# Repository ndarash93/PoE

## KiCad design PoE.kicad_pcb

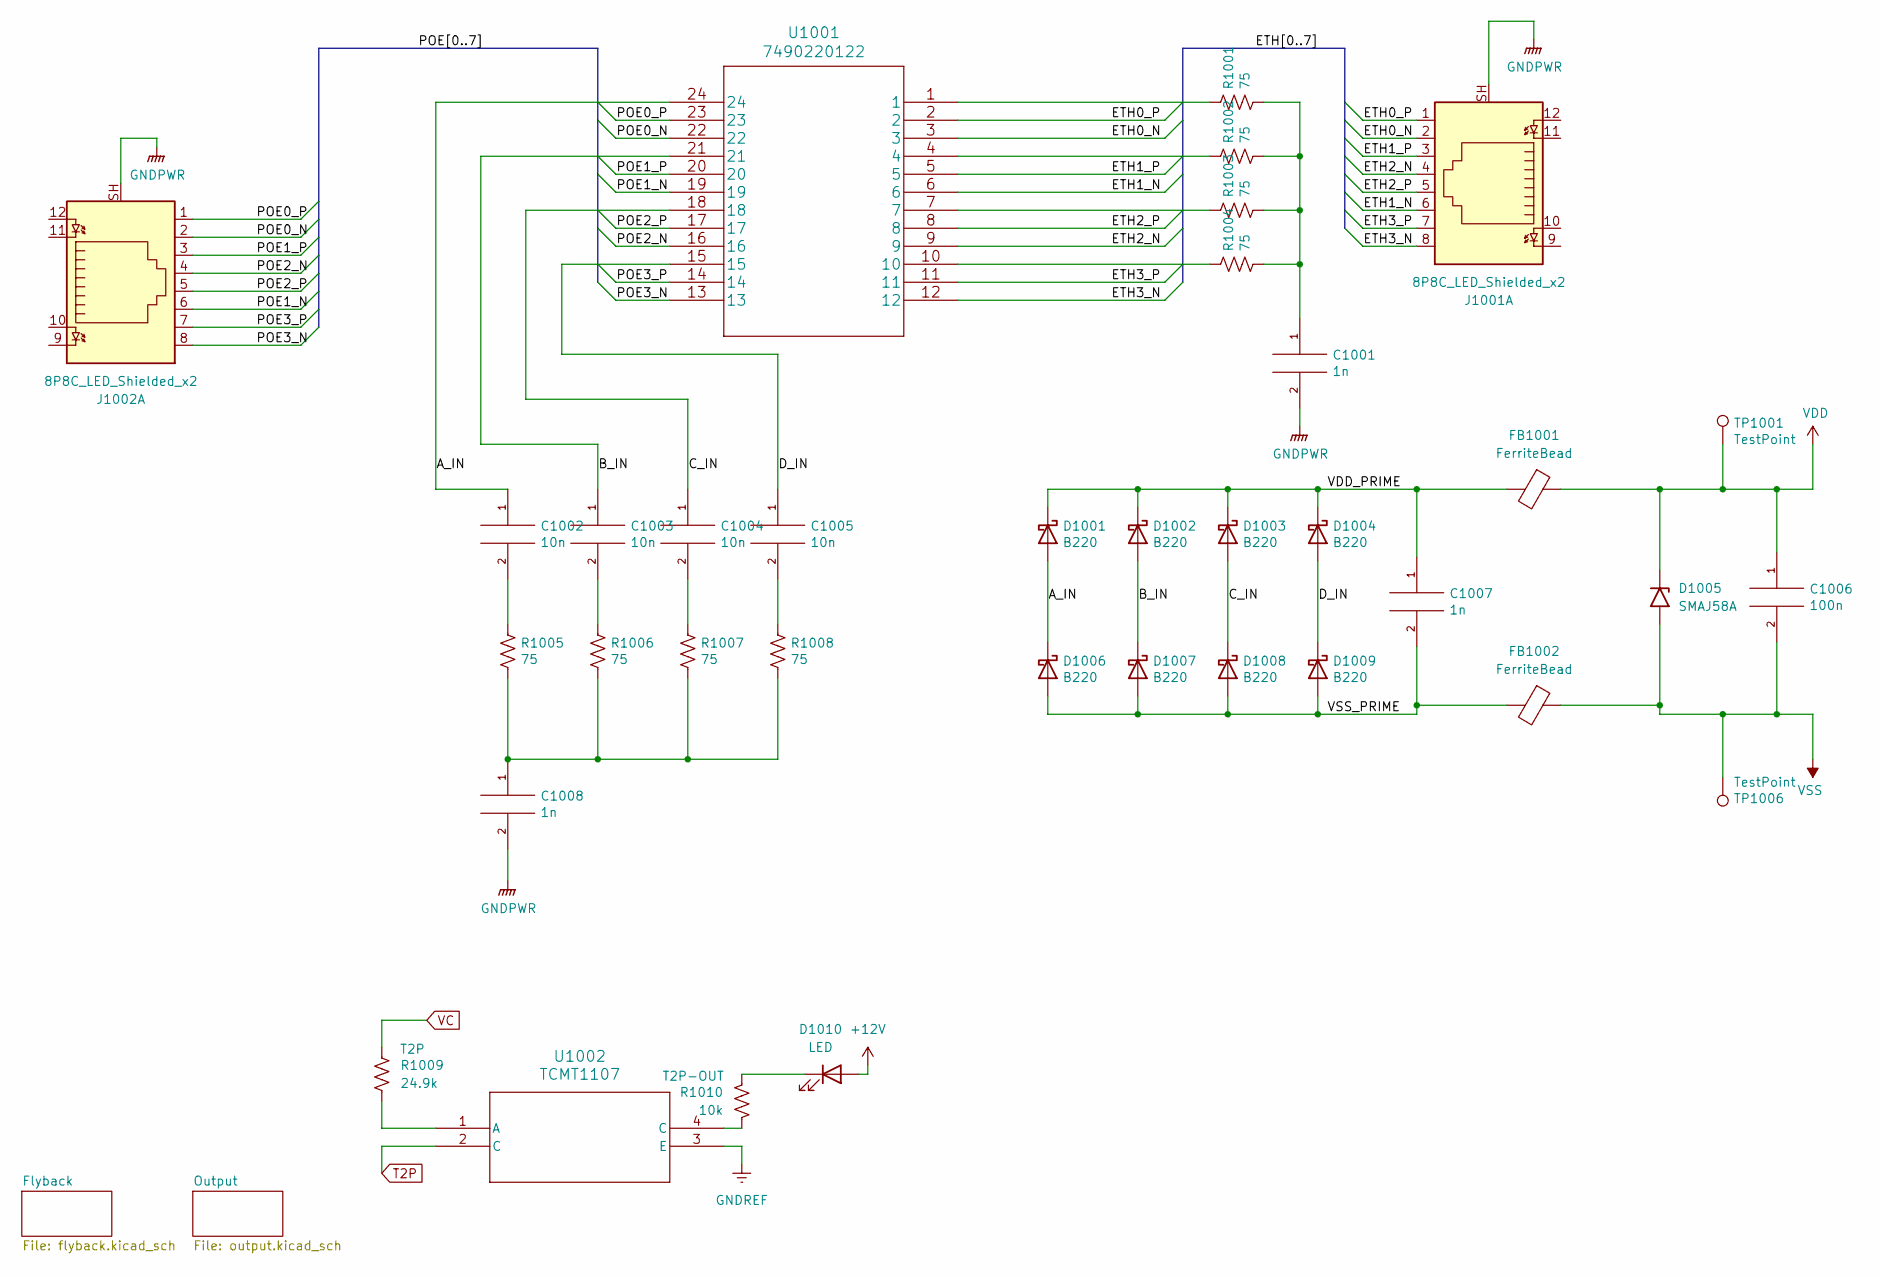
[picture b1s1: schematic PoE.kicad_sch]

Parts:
C1001, C1007, C1008: 1n; C_0805_2012Metric
C1002, C1003, C1004, C1005: 10n; C_0805_2012Metric
C1006: 100n; C_0805_2012Metric
D1001, D1002, D1003, D1004, D1006, D1007, D1008, D1009: B220; D_SMB
D1005: SMAJ58A; D_SMA
D1010: LED; LED_0805_2012Metric
FB1001, FB1002: FerriteBead; R_0805_2012Metric
J1001, J1002: 8P8C_LED_Shielded_x2; CONN12_ARJM11B1-009-AB-EW2_ABR
R1001, R1002, R1003, R1004, R1005, R1006, R1007, R1008: 75; R_0805_2012Metric
R1009: 24.9k; R_0805_2012Metric
R1010: 10k; R_0805_2012Metric
TP1001, TP1006: TestPoint; TestPoint_Pad_1.0x1.0mm
U1001: 7490220122
U1002: TCMT1107; SSOP4_4P40X2P85_VIS

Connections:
+12V: D1010.2 (A); also elsewhere on the board
/A_IN: C1002.1, D1001.2 (A), D1006.1 (K), U1001.24
/B_IN: C1003.1, D1002.2 (A), D1007.1 (K), U1001.21
/C_IN: C1004.1, D1003.2 (A), D1008.1 (K), U1001.18
/D_IN: C1005.1, D1004.2 (A), D1009.1 (K), U1001.15
/ETH0_N: J1001.2, U1001.3
/ETH0_P: J1001.1, U1001.2
/ETH1_N: J1001.6, U1001.6
/ETH1_P: J1001.3, U1001.5
/ETH2_N: J1001.4, U1001.9
/ETH2_P: J1001.5, U1001.8
/ETH3_N: J1001.8, U1001.12
/ETH3_P: J1001.7, U1001.11
/POE0_N: J1002.2, U1001.22
/POE0_P: J1002.1, U1001.23
/POE1_N: J1002.6, U1001.19
/POE1_P: J1002.3, U1001.20
/POE2_N: J1002.4, U1001.16
/POE2_P: J1002.5, U1001.17
/POE3_N: J1002.8, U1001.13
/POE3_P: J1002.7, U1001.14
/VDD_PRIME: C1007.1, D1001.1 (K), D1002.1 (K), D1003.1 (K), D1004.1 (K), FB1001.2
/VSS_PRIME: C1007.2, D1006.2 (A), D1007.2 (A), D1008.2 (A), D1009.2 (A), FB1002.2
GNDPWR: C1001.2, C1008.2, J1001.SH, J1002.SH
GNDREF: U1002.3 (E); also elsewhere on the board
unnamed: C1001.1, R1001.2, R1002.2, R1003.2, R1004.2
unnamed: C1002.2, R1005.1
unnamed: C1003.2, R1006.1
unnamed: C1004.2, R1007.1
unnamed: C1005.2, R1008.1
unnamed: C1008.1, R1005.2, R1006.2, R1007.2, R1008.2
unnamed: D1010.1 (K), R1010.1
unnamed: R1001.1, U1001.1
unnamed: R1002.1, U1001.4
unnamed: R1003.1, U1001.7
unnamed: R1004.1, U1001.10
unnamed: R1010.2, U1002.4 (C)
unnamed: R1009.2, U1002.1 (A)
T2P: U1002.2 (C); also elsewhere on the board
VC: R1009.1; also elsewhere on the board
VDD: C1006.1, D1005.1 (A1), FB1001.1, TP1001.1; also elsewhere on the board
VSS: C1006.2, D1005.2 (A2), FB1002.1, TP1006.1; also elsewhere on the board

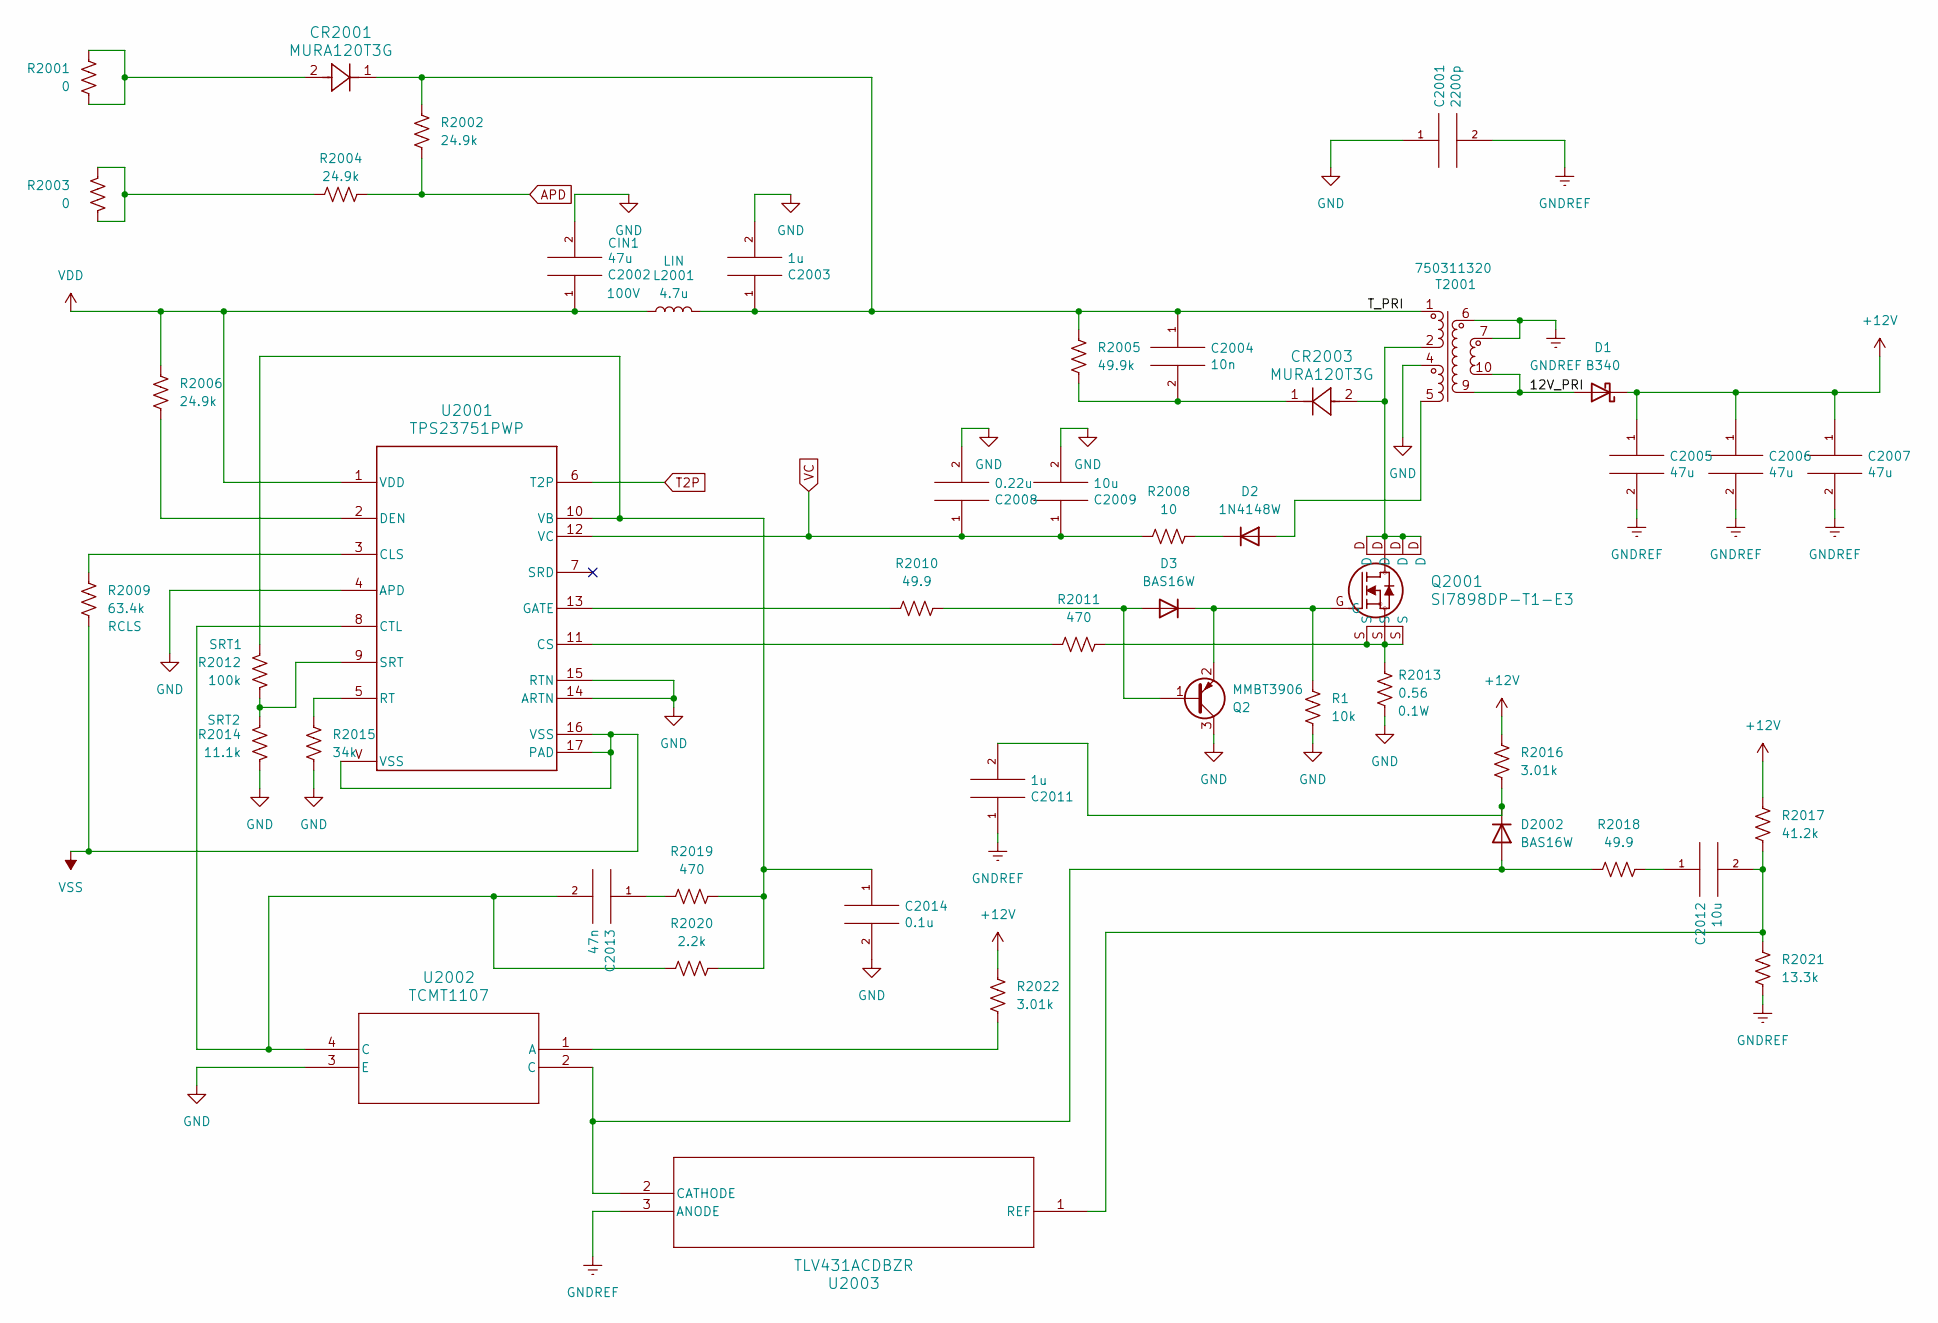
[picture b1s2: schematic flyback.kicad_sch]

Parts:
C2001: 2200p; C_0805_2012Metric
C2002: 47u; CAP_WCAP-ASLI_06p3X05p5_WRE; Voltage 100V
C2003: 1u; CAP_WCAP-ASLI_06p3X05p5_WRE
C2004: 10n; C_0805_2012Metric
C2005, C2006, C2007: 47u; CAP_WCAP-ASLI_06p3X05p5_WRE
C2008: 0.22u; C_0805_2012Metric
C2009, C2012: 10u; C_0805_2012Metric
C2011: 1u; C_0805_2012Metric
C2013: 47n; C_0805_2012Metric
C2014: 0.1u; C_0805_2012Metric
CR2001, CR2003: MURA120T3G; DIODE_TVS1SMAS5_4P57X2P92_ONS
D1: B340; D_SMC
D2: 1N4148W; D_SOD-123
D3, D2002: BAS16W; SOT-323_SC-70
L2001: 4.7u; L_Abracon_ASPI-4030S
Q2: MMBT3906; SOT-23
Q2001: SI7898DP-T1-E3; MOSFET_50DP-T1-E3_VIS
R1: 10k; R_0805_2012Metric
R2001, R2003: 0; R_0805_2012Metric
R2002, R2004, R2006: 24.9k; R_0805_2012Metric
R2005: 49.9k; R_0805_2012Metric
R2008: 10; R_0805_2012Metric
R2009: 63.4k; R_0805_2012Metric
R2010, R2018: 49.9; R_0805_2012Metric
R2011, R2019: 470; R_0805_2012Metric
R2012: 100k; R_0805_2012Metric
R2013: 0.56; R_0805_2012Metric
R2014: 11.1k; R_0805_2012Metric
R2015: 34k; R_0805_2012Metric
R2016, R2022: 3.01k; R_0805_2012Metric
R2017: 41.2k; R_0805_2012Metric
R2020: 2.2k; R_0805_2012Metric
R2021: 13.3k; R_0805_2012Metric
T2001: 750311320
U2001: TPS23751PWP; PWP0016J_N
U2002: TCMT1107; SSOP4_4P40X2P85_VIS
U2003: TLV431ACDBZR; DBZ3

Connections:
+12V: C2005.1, C2006.1, C2007.1, D1.1 (K), R2016.2, R2017.1, R2022.2; also elsewhere on the board
/Flyback/12V_PRI: D1.2 (A), T2001.9, T2001.10
/Flyback/T_PRI: C2003.1, C2004.1, CR2001.1, L2001.2, R2002.1, R2005.1, T2001.1
APD: R2002.2, R2004.1
GND: C2001.1, C2002.2, C2003.2, C2008.2, C2009.2, C2014.2, Q2.3 (C), R1.2, R2013.2, R2014.2, R2015.2, T2001.4, U2001.4 (APD), U2001.14 (ARTN), U2001.15 (RTN), U2002.3 (E)
GNDREF: C2001.2, C2005.2, C2006.2, C2007.2, C2011.1, R2021.2, T2001.6, T2001.7, U2003.3 (ANODE); also elsewhere on the board
unnamed: C2004.2, CR2003.1, R2005.2
unnamed: C2012.1, R2018.1
unnamed: C2013.1, R2019.2
unnamed: CR2001.2, R2001.1, R2001.2
unnamed: CR2003.2, Q2001.D, T2001.2
unnamed: D2.2 (A), T2001.5
unnamed: D2.1 (K), R2008.1
unnamed: D3.1 (A), Q2.1 (B), R2010.1
unnamed: D3.3 (K), Q2.2 (E), Q2001.G, R1.1
unnamed: D2002.1 (A), R2018.2, U2002.2 (C), U2003.2 (CATHODE)
unnamed: C2011.2, D2002.3 (K), R2016.1
unnamed: Q2001.S, R2011.1, R2013.1
unnamed: R2003.1, R2003.2, R2004.2
unnamed: R2009.1, U2001.3 (CLS)
unnamed: R2011.2, U2001.11 (CS)
unnamed: C2013.2, R2020.2, U2001.8 (CTL), U2002.4 (C)
unnamed: R2006.2, U2001.2 (DEN)
unnamed: R2010.2, U2001.13 (GATE)
unnamed: R2015.1, U2001.5 (RT)
unnamed: R2012.2, R2014.1, U2001.9 (SRT)
unnamed: C2014.1, R2012.1, R2019.1, R2020.1, U2001.10 (VB)
unnamed: R2022.1, U2002.1 (A)
unnamed: C2012.2, R2017.2, R2021.1, U2003.1 (REF)
T2P: U2001.6 (T2P); also elsewhere on the board
VC: C2008.1, C2009.1, R2008.2, U2001.12 (VC); also elsewhere on the board
VDD: C2002.1, L2001.1, R2006.1, U2001.1 (VDD); also elsewhere on the board
VSS: R2009.2, U2001.16 (VSS), U2001.17 (PAD), U2001.V (VSS); also elsewhere on the board

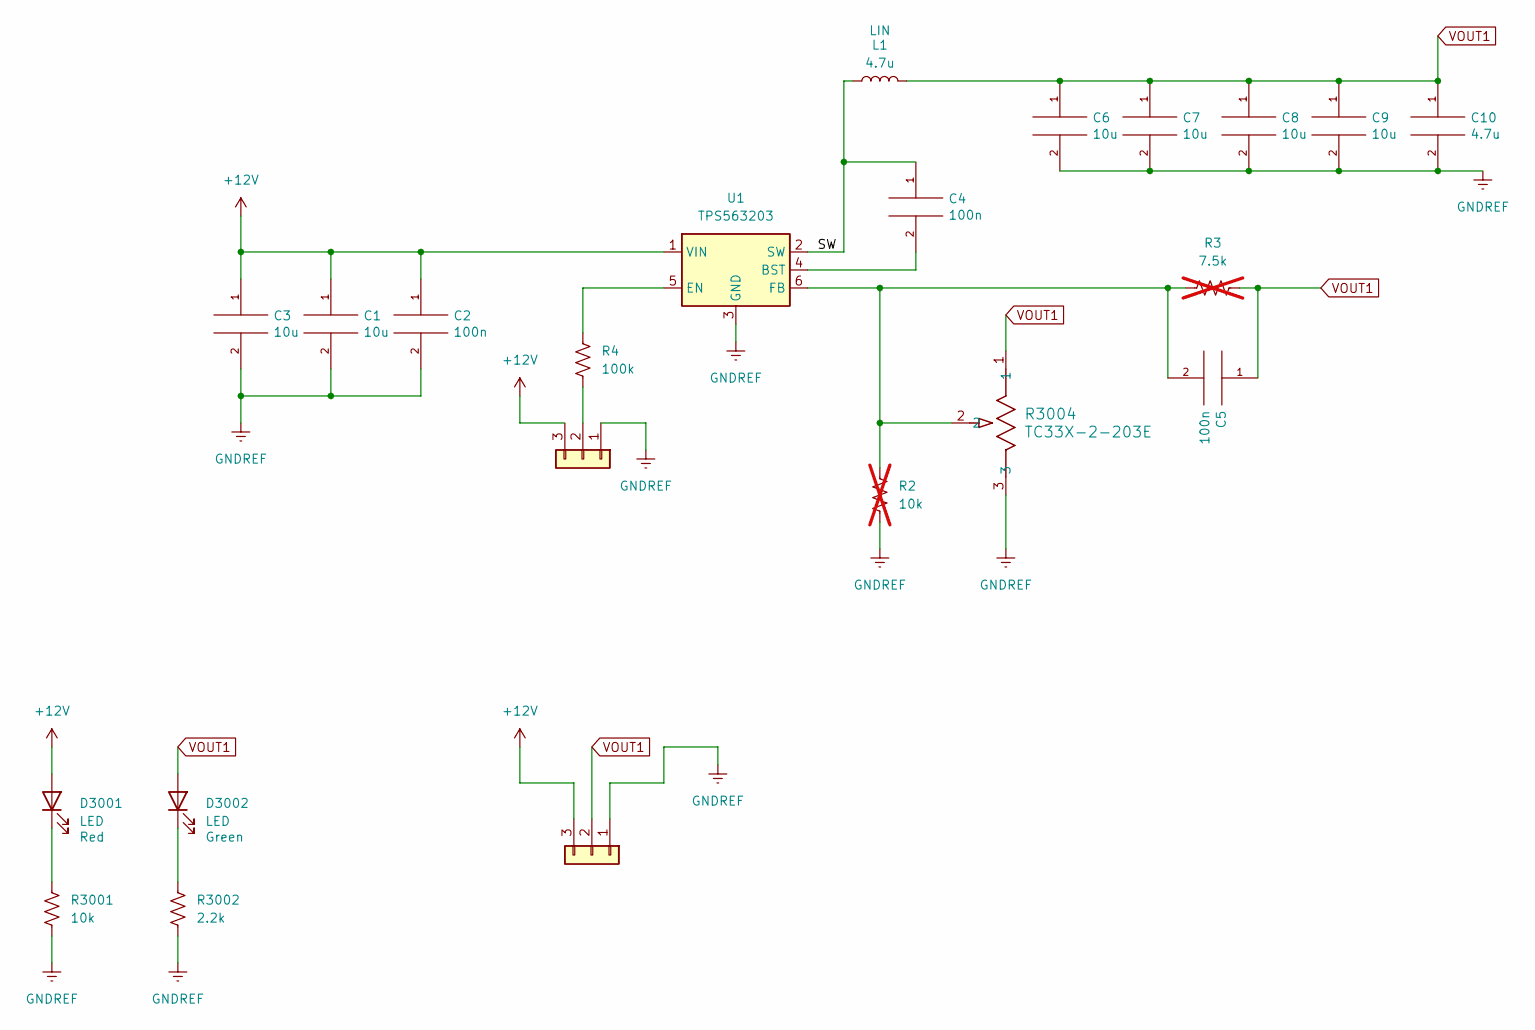
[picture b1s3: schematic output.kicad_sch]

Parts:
C1, C3, C6, C7, C8, C9: 10u; C_0805_2012Metric
C2, C4, C5: 100n; C_0805_2012Metric
C10: 4.7u; C_0805_2012Metric
D3001, D3002: LED; LED_0805_2012Metric
J1, J3001: Conn_01x03; 1x03
L1: 4.7u; L_Abracon_ASPI-4030S
R2: 10k; R_0805_2012Metric; not fitted
R3: 7.5k; R_0805_2012Metric; not fitted
R4: 100k; R_0805_2012Metric
R3001: 10k; R_0805_2012Metric
R3002: 2.2k; R_0805_2012Metric
R3004: TC33X-2-203E; Potentiometer_Bourns_TC33X_Vertical
U1: TPS563203; SOT-563

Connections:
+12V: C1.1, C2.1, C3.1, D3001.2 (A), J1.3, J3001.3, U1.1 (VIN); also elsewhere on the board
/Output/SW: C4.1, L1.1, U1.2 (SW)
GNDREF: C1.2, C2.2, C3.2, C6.2, C7.2, C8.2, C9.2, C10.2, J1.1, J3001.1, R2.1, R3001.1, R3002.1, R3004.3, U1.3 (GND); also elsewhere on the board
unnamed: D3001.1 (K), R3001.2
unnamed: D3002.1 (K), R3002.2
unnamed: J1.2, R4.1
unnamed: C4.2, U1.4 (BST)
unnamed: R4.2, U1.5 (EN)
unnamed: C5.2, R2.2, R3.1, R3004.2, U1.6 (FB)
VOUT1: C5.1, C6.1, C7.1, C8.1, C9.1, C10.1, D3002.2 (A), J3001.2, L1.2, R3.2, R3004.1

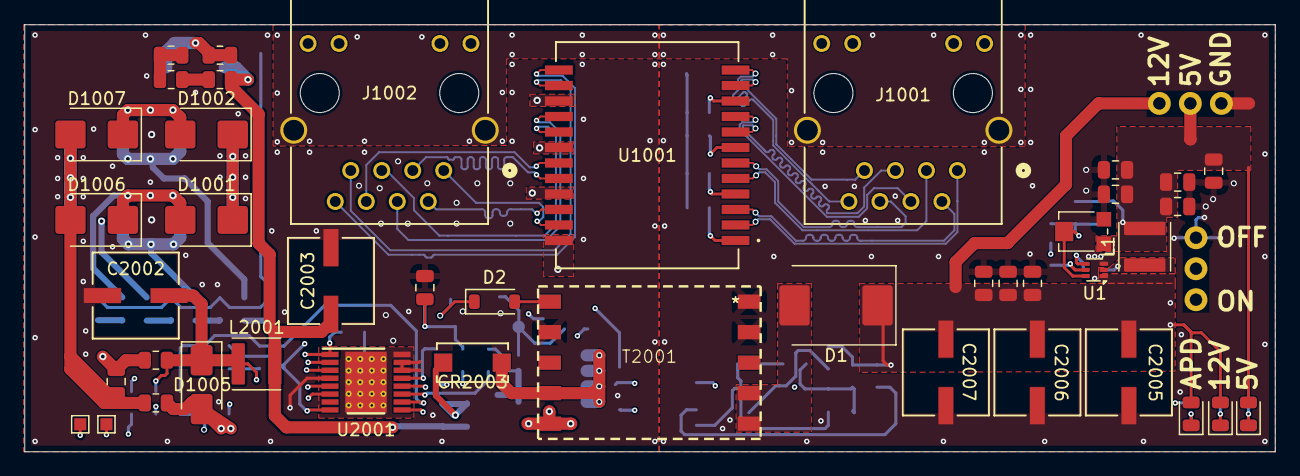
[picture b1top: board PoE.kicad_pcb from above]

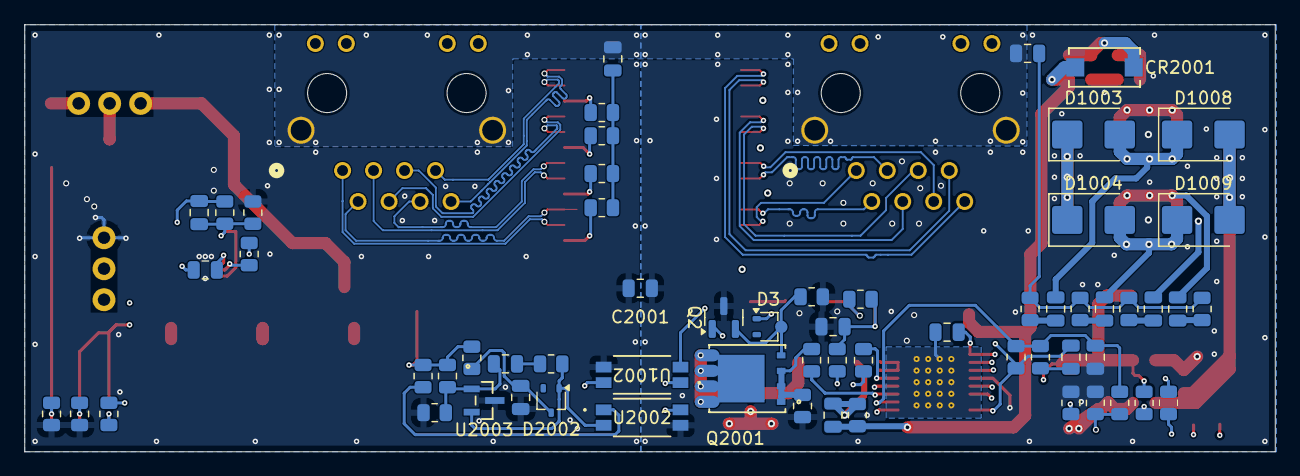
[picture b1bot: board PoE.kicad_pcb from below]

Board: 4 copper layers, 102.5 x 35.0 mm, 106 parts (61 on the bottom side), 77 nets.

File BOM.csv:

"Reference","Value","Datasheet","Footprint","Qty","DNP"
"C1,C3,C6,C7,C8,C9,C2009,C2012","10u","~","-- mixed values --","8",""
"C2,C4,C5,C1006","100n","~","Capacitor_SMD:C_0805_2012Metric","4",""
"C10,L1,L2001","4.7u","~","-- mixed values --","3",""
"C1001,C1007,C1008","1n","~","Capacitor_SMD:C_0805_2012Metric","3",""
"C1002,C1003,C1004,C1005,C2004","10n","~","Capacitor_SMD:C_0805_2012Metric","5",""
"C2001","2200p","~","Capacitor_SMD:C_0805_2012Metric","1",""
"C2002,C2005,C2006,C2007","47u","~","footprints:CAP_WCAP-ASLI_06p3X05p5_WRE","4",""
"C2003,C2011","1u","~","Capacitor_SMD:C_0805_2012Metric","2",""
"C2008","0.22u","~","Capacitor_SMD:C_0805_2012Metric","1",""
"C2013","47n","~","Capacitor_SMD:C_0805_2012Metric","1",""
"C2014","0.1u","~","Capacitor_SMD:C_0805_2012Metric","1",""
"CR2001,CR2003","MURA120T3G","MURA120T3G","footprints:DIODE_TVS1SMAS5_4P57X2P92_ONS","2",""
"D1","B340","http://www.jameco.com/Jameco/Products/ProdDS/1538777.pdf","Diode_SMD:D_SMC","1",""
"D2","1N4148W","https://www.vishay.com/docs/85748/1n4148w.pdf","Diode_SMD:D_SOD-123","1",""
"D3,D2002","BAS16W","https://assets.nexperia.com/documents/data-sheet/BAS16_SER.pdf","Package_TO_SOT_SMD:SOT-323_SC-70","2",""
"D1001,D1002,D1003,D1004,D1006,D1007,D1008,D1009","B220","http://www.jameco.com/Jameco/Products/ProdDS/1538777.pdf","Diode_SMD:D_SMB","8",""
"D1005","SMAJ58A","https://www.littelfuse.com/media?resourcetype=datasheets&ite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","Diode_SMD:D_SMA","1",""
"D1010,D3001,D3002","LED","~","LED_SMD:LED_0805_2012Metric","3",""
"FB1001,FB1002","FerriteBead","~","Resistor_SMD:R_0805_2012Metric","2",""
"J1,J3001","Conn_01x03","~","SparkFun-Connector:1x03","2",""
"J1001,J1002","8P8C_LED_Shielded_x2","~","footprints:CONN12_ARJM11B1-009-AB-EW2_ABR","2",""
"Q2","MMBT3906","https://www.onsemi.com/pdf/datasheet/pzt3906-d.pdf","Package_TO_SOT_SMD:SOT-23","1",""
"Q2001","SI7898DP-T1-E3","SI7898DP-T1-E3","footprints:MOSFET_50DP-T1-E3_VIS","1",""
"R1,R1010,R3001","10k","~","Resistor_SMD:R_0805_2012Metric","3",""
"R2","10k","~","Resistor_SMD:R_0805_2012Metric","1","DNP"
"R3","7.5k","~","Resistor_SMD:R_0805_2012Metric","1","DNP"
"R4,R2012","100k","~","Resistor_SMD:R_0805_2012Metric","2",""
"R1001,R1002,R1003,R1004,R1005,R1006,R1007,R1008","75","~","Resistor_SMD:R_0805_2012Metric","8",""
"R1009,R2002,R2004,R2006","24.9k","~","Resistor_SMD:R_0805_2012Metric","4",""
"R2001,R2003","0","-- mixed values --","Resistor_SMD:R_0805_2012Metric","2",""
"R2005","49.9k","~","Resistor_SMD:R_0805_2012Metric","1",""
"R2008","10","~","Resistor_SMD:R_0805_2012Metric","1",""
"R2009","63.4k","~","Resistor_SMD:R_0805_2012Metric","1",""
"R2010","43.2","~","Resistor_SMD:R_0805_2012Metric","1",""
"R2011","332","~","Resistor_SMD:R_0805_2012Metric","1",""
"R2013","0.56","~","Resistor_SMD:R_0805_2012Metric","1",""
"R2014","11.1k","~","Resistor_SMD:R_0805_2012Metric","1",""
"R2015","34k","~","Resistor_SMD:R_0805_2012Metric","1",""
"R2016,R2022","3.01k","~","Resistor_SMD:R_0805_2012Metric","2",""
"R2017","41.2k","~","Resistor_SMD:R_0805_2012Metric","1",""
"R2018","49.9","~","Resistor_SMD:R_0805_2012Metric","1",""
"R2019","402","~","Resistor_SMD:R_0805_2012Metric","1",""
"R2020","2k","~","Resistor_SMD:R_0805_2012Metric","1",""
"R2021","13.3k","~","Resistor_SMD:R_0805_2012Metric","1",""
"R3002","2.2k","~","Resistor_SMD:R_0805_2012Metric","1",""
"R3004","TC33X-2-203E","TC33X-2-203E","Potentiometer_SMD:Potentiometer_Bourns_TC33X_Vertical","1",""
"T2001","~","https://www.we-online.com/components/products/datasheet/7503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","footprints:750311320","1",""
"TP1001,TP1006","TestPoint","~","SparkFun-Connector:TestPoint-1.0mm","2",""
"U1","TPS563203","https://www.ti.com/lit/ds/symlink/tps563203.pdf","Package_TO_SOT_SMD:SOT-563","1",""
"U1001","7490220122","","footprints:7490220122","1",""
"U1002,U2002","TCMT1107","TCMT1107","footprints:SSOP4_4P40X2P85_VIS","2",""
"U2001","TPS23751PWP","TPS23751PWP","footprints:PWP0016J_N","1",""
"U2003","TLV431ACDBZR","TLV431ACDBZR","footprints:DBZ3","1",""

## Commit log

2024-07-29 Added sheet for flyback
2024-07-30 Working on flyback diode
2024-07-31 Added basic SPICE sim
2024-07-31 More updates, added bus
2024-08-01 Minor updates and adding footprints
2024-08-02 Found footprints
2024-08-03 Updating layout
2024-08-04 Changed all passive footprints to 0805
2024-08-04 Starting Layout
2024-08-05 Still needs a lot of work
2024-08-06 No longer tracking the backups
2024-08-06 Added power planes
2024-08-07 Added routing
2024-08-07 New layout attempt
2024-08-07 No change
2024-08-08 Changed main FET
2024-08-08 Not tracking per process files
2024-08-08 Stopped tracking kicad_prl
2024-08-08 More routing
2024-08-09 Added more routing
2024-08-10 Finished routing now needs review
2024-08-11 Gave up on advanced sim
2024-08-11 Added buck
2024-08-11 Stopped tracking backups
2024-08-12 Added LEDs for status
2024-08-13 Updated layout and constraints
2024-08-13 Minor changes
2024-08-13 Redoing ethernet routing
2024-08-14 Fixing ethernet routing
2024-08-15 Routing updates to ethernet
2024-08-16 Updated clearence of GND and moved stitching vias around
2024-08-18 Added BOM, fixed routing mistakes
2024-08-19 Prepping BOM
2024-08-19 Changed gitignore for gerber stuff
2024-08-20 Fine tuning resistor values
2024-08-21 Cleaning up repo
2024-08-21 Cleaning
2024-08-21 cleaning more
2024-08-21 Even more cleaning

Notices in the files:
parts and their libraries:
Copyright 2016 Accelerated Designs. All rights reserved.
